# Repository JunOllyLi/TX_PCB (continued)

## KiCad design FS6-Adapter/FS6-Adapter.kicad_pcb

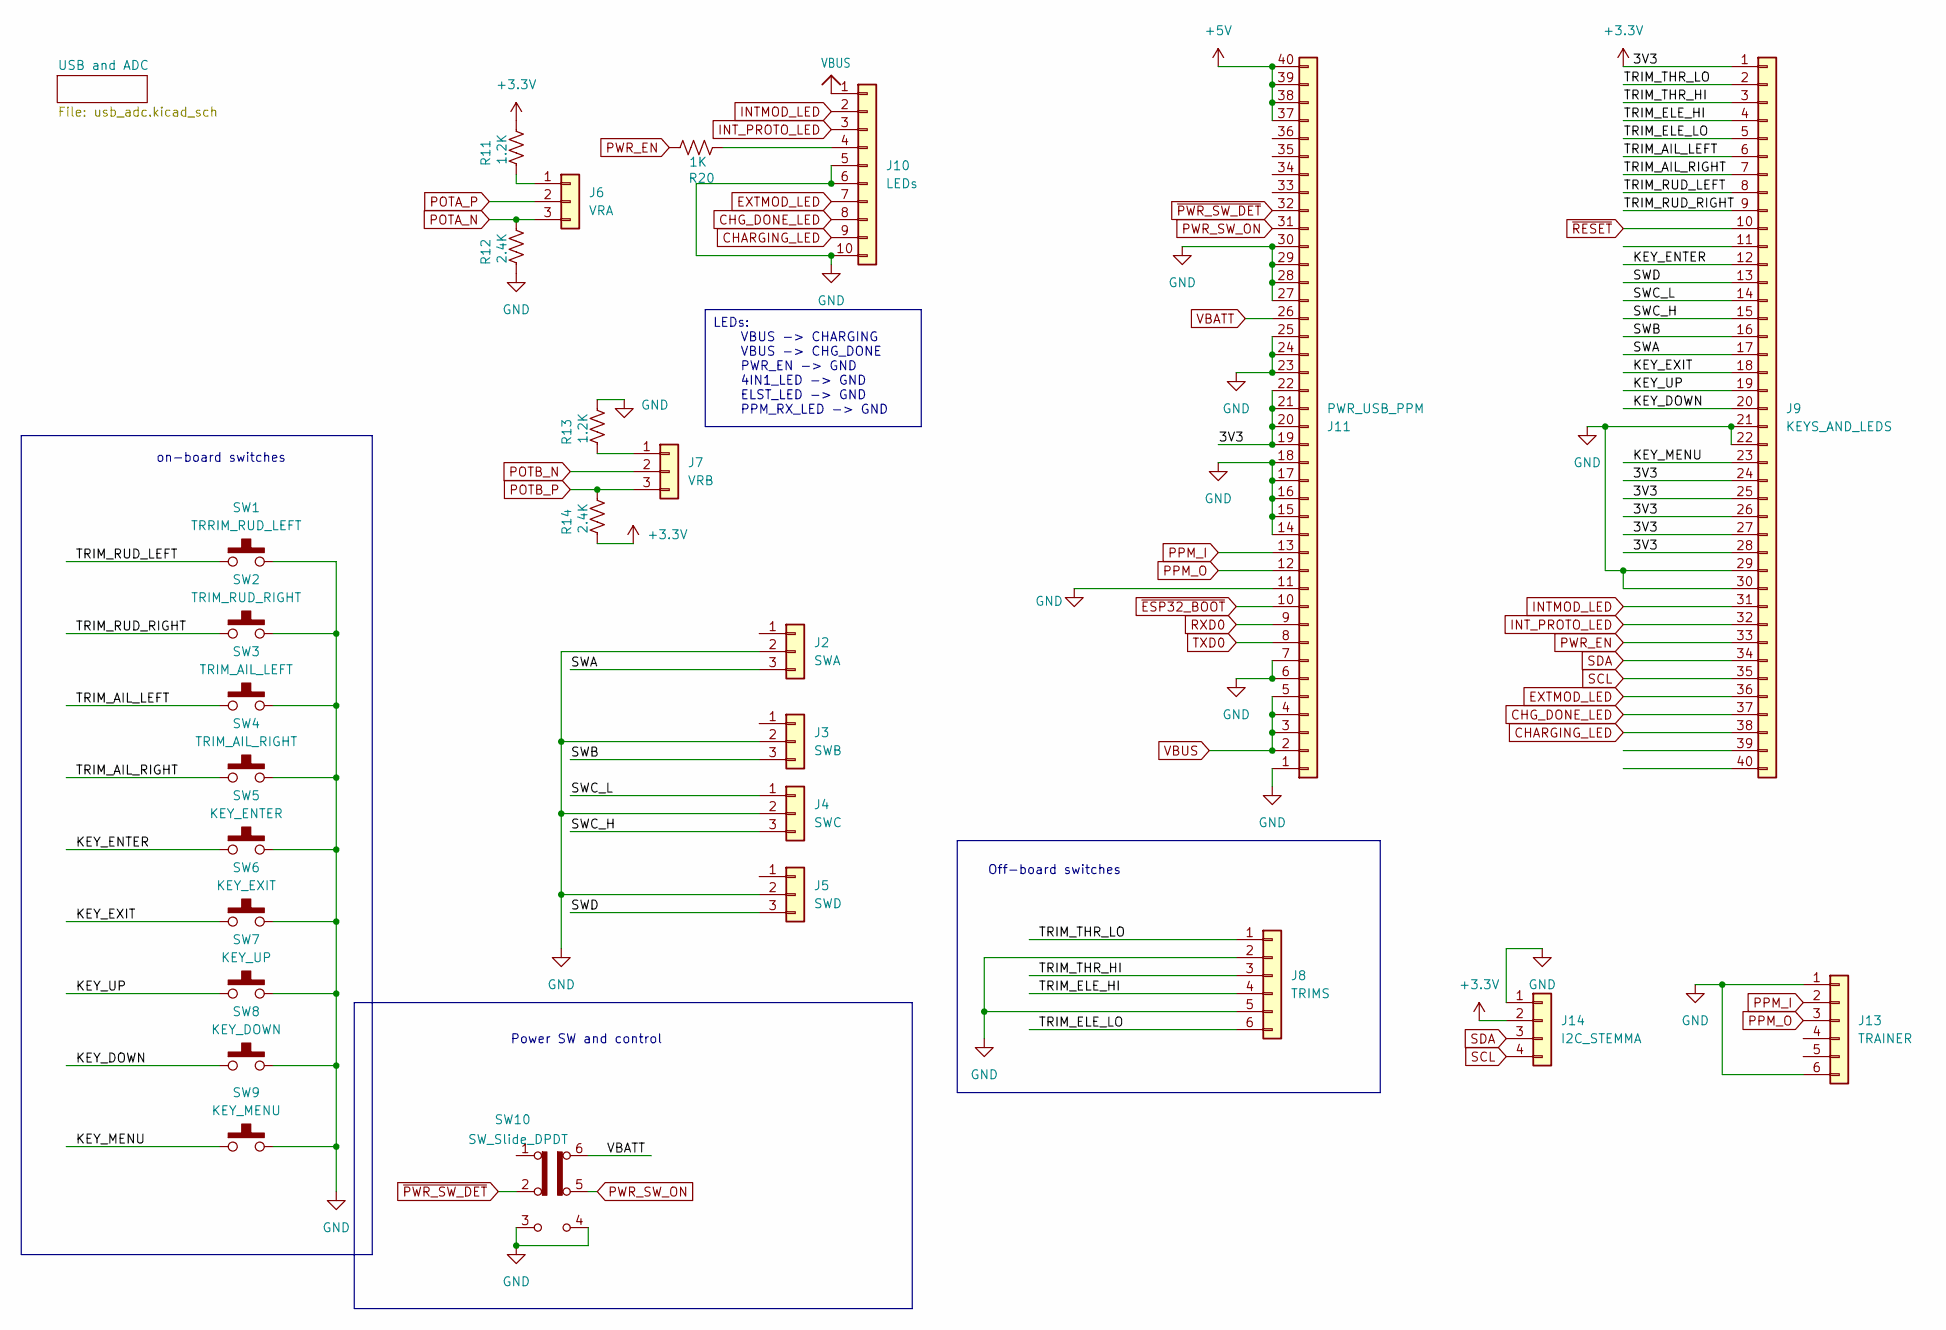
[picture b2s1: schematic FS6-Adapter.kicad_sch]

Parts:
J2: SWA; JST_GH_BM03B-GHS-TBT_1x03-1MP_P1.25mm_Vertical
J3: SWB; JST_GH_BM03B-GHS-TBT_1x03-1MP_P1.25mm_Vertical
J4: SWC; JST_GH_BM03B-GHS-TBT_1x03-1MP_P1.25mm_Vertical
J5: SWD; JST_GH_BM03B-GHS-TBT_1x03-1MP_P1.25mm_Vertical
J6: VRA; JST_GH_BM03B-GHS-TBT_1x03-1MP_P1.25mm_Vertical
J7: VRB; JST_GH_BM03B-GHS-TBT_1x03-1MP_P1.25mm_Vertical
J8: TRIMS; JST_ZH1.50mm_6_PIN_Vertical
J9: KEYS_AND_LEDS; FPC_40PIN_TOP
J10: LEDs; JST_GH_BM10B-GHS-TBT_1x10-1MP_P1.25mm_Vertical
J11: PWR_USB_PPM; FPC_40PIN_TOP
J13: TRAINER; JST_ZH1.50mm_6_PIN_Vertical
J14: I2C_STEMMA; JST_SH_BM04B-SRSS-TB_1x04-1MP_P1.00mm_Vertical
R11, R13: 1.2K; R_0603_1608Metric_Pad0.98x0.95mm_HandSolder
R12, R14: 2.4K; R_0603_1608Metric_Pad0.98x0.95mm_HandSolder
R20: 1K; R_0603_1608Metric_Pad0.98x0.95mm_HandSolder
SW1: TRRIM_RUD_LEFT; SW_6.2mm
SW2: TRIM_RUD_RIGHT; SW_6.2mm
SW3: TRIM_AIL_LEFT; SW_6.2mm
SW4: TRIM_AIL_RIGHT; SW_6.2mm
SW5: KEY_ENTER; SW_6.2mm
SW6: KEY_EXIT; SW_6.2mm
SW7: KEY_UP; SW_6.2mm
SW8: KEY_DOWN; SW_6.2mm
SW9: KEY_MENU; SW_12mm
SW10: SW_Slide_DPDT; SW_SLIDE_DPDT_7mm

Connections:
+3.3V: J9.1, J9.24, J9.25, J9.26, J9.27, J9.28, J11.19, J11.20, J11.21, J11.22, J14.2, R11.2, R14.1; also elsewhere on the board
+5V: J11.37, J11.38, J11.39, J11.40
/KEY_DOWN: J9.20, SW8.1 (A), SW8.2 (B)
/KEY_ENTER: J9.12, SW5.1 (A), SW5.2 (B)
/KEY_EXIT: J9.18, SW6.1 (A), SW6.2 (B)
/KEY_MENU: J9.23, SW9.1 (A), SW9.2 (B)
/KEY_UP: J9.19, SW7.1 (A), SW7.2 (B)
/SWA: J2.3, J9.17
/SWB: J3.3, J9.16
/SWC_H: J4.3, J9.15
/SWC_L: J4.1, J9.14
/SWD: J5.3, J9.13
/TRIM_AIL_LEFT: J9.6, SW3.1 (A), SW3.2 (B)
/TRIM_AIL_RIGHT: J9.7, SW4.1 (A), SW4.2 (B)
/TRIM_ELE_HI: J8.4, J9.4
/TRIM_ELE_LO: J8.6, J9.5
/TRIM_RUD_LEFT: J9.8, SW1.1 (A), SW1.2 (B)
/TRIM_RUD_RIGHT: J9.9, SW2.1 (A), SW2.2 (B)
/TRIM_THR_HI: J8.3, J9.3
/TRIM_THR_LO: J8.1, J9.2
CHARGING_LED: J9.38, J10.9
CHG_DONE_LED: J9.37, J10.8
EXTMOD_LED: J9.36, J10.7
GND: J2.2, J3.2, J4.2, J5.2, J8.2, J8.5, J9.21, J9.22, J9.29, J9.30, J10.5, J10.6, J10.10, J11.1, J11.6, J11.7, J11.11, J11.14, J11.15, J11.16, J11.17, J11.18, J11.23, J11.24, J11.25, J11.27, J11.28, J11.29, J11.30, J13.1, J13.6, J14.1, R12.1, R13.2, SW1.3 (C), SW1.4 (D), SW2.3 (C), SW2.4 (D), SW3.3 (C), SW3.4 (D), SW4.3 (C), SW4.4 (D), SW5.3 (C), SW5.4 (D), SW6.3 (C), SW6.4 (D), SW7.3 (C), SW7.4 (D), SW8.3 (C), SW8.4 (D), SW9.3 (C), SW9.4 (D), SW10.3 (C), SW10.4 (A); also elsewhere on the board
INTMOD_LED: J9.31, J10.2
INT_PROTO_LED: J9.32, J10.3
unnamed: J6.1, R11.1
unnamed: J7.1, R13.1
unnamed: J10.4, R20.1
POTA_N: J6.3, R12.2; also elsewhere on the board
POTA_P: J6.2; also elsewhere on the board
POTB_N: J7.2; also elsewhere on the board
POTB_P: J7.3, R14.2; also elsewhere on the board
PPM_I: J11.13, J13.2
PPM_O: J11.12, J13.3
PWR_EN: J9.33, R20.2
PWR_SW_ON: J11.31, SW10.5 (B)
RXD0: J11.9; also elsewhere on the board
SCL: J9.35, J14.4; also elsewhere on the board
SDA: J9.34, J14.3; also elsewhere on the board
TXD0: J11.8; also elsewhere on the board
VBATT: J11.26, SW10.6 (C); also elsewhere on the board
VBUS: J10.1, J11.2, J11.3, J11.4, J11.5; also elsewhere on the board
~ESP32_BOOT: J11.10; also elsewhere on the board
~PWR_SW_DET: J11.32, SW10.2 (B)
~RESET: J9.10; also elsewhere on the board

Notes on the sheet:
LEDs: VBUS -> CHARGING VBUS -> CHG_DONE PWR_EN -> GND 4IN1_LED -> GND ELST_LED -> GND PPM_RX_LED -> GND
on-board switches
Power SW and control
Off-board switches

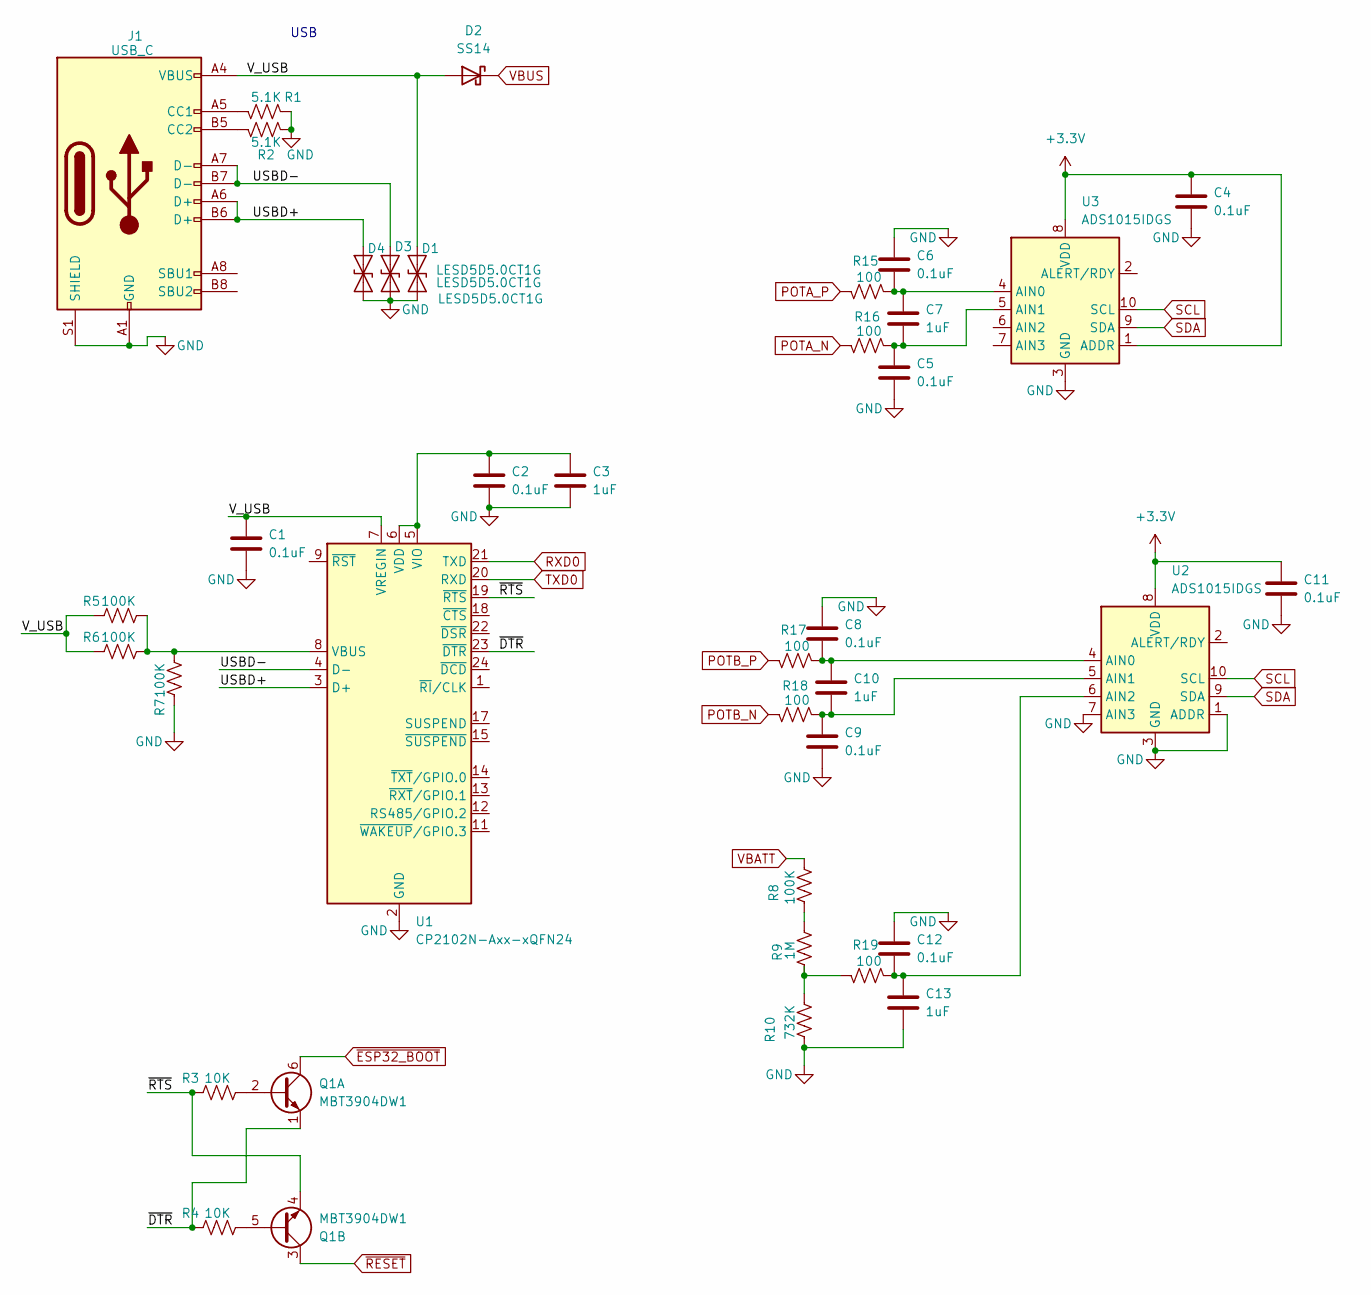
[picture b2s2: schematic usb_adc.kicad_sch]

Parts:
C1, C2, C4, C5, C6, C8, C9, C11, C12: 0.1uF; C_0603_1608Metric_Pad1.08x0.95mm_HandSolder
C3, C7, C10, C13: 1uF; C_0603_1608Metric_Pad1.08x0.95mm_HandSolder
D1, D3, D4: LESD5D5.0CT1G; D_SOD-523
D2: SS14; D_SMA
J1: USB_C; my_USB_C_Receptacle_GCT_USB4105-xx-A_16P_TopMnt_Horizontal
Q1: MBT3904DW1; SOT-363_SC-70-6
R1, R2: 5.1K; R_0603_1608Metric_Pad0.98x0.95mm_HandSolder
R3, R4: 10K; R_0603_1608Metric_Pad0.98x0.95mm_HandSolder
R5, R6, R7, R8: 100K; R_0603_1608Metric_Pad0.98x0.95mm_HandSolder
R9: 1M; R_0603_1608Metric_Pad0.98x0.95mm_HandSolder
R10: 732K; R_0603_1608Metric_Pad0.98x0.95mm_HandSolder
R15, R16, R17, R18, R19: 100; R_0603_1608Metric_Pad0.98x0.95mm_HandSolder
U1: CP2102N-Axx-xQFN24; QFN-24-1EP_4x4mm_P0.5mm_EP2.6x2.6mm
U2, U3: ADS1015IDGS; TSSOP-10_3x3mm_P0.5mm

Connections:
+3.3V: C4.1, C11.1, U2.8 (VDD), U3.1 (ADDR), U3.8 (VDD); also elsewhere on the board
/USB and ADC/USBD+: D4.2 (A2), J1.A6 (D+), J1.B6 (D+), U1.3 (D+)
/USB and ADC/USBD-: D3.2 (A2), J1.A7 (D-), J1.B7 (D-), U1.4 (D-)
/USB and ADC/V_USB: C1.1, D1.2 (A2), D2.2 (A), J1.A4 (VBUS), J1.A9 (VBUS), J1.B4 (VBUS), J1.B9 (VBUS), R5.1, R6.1, U1.7 (VREGIN)
/USB and ADC/~DTR: Q1.1 (E1), R4.1, U1.23 (~DTR)
/USB and ADC/~RTS: Q1.4 (E2), R3.1, U1.19 (~RTS)
GND: C1.2, C2.2, C3.2, C4.2, C5.2, C6.1, C8.1, C9.2, C11.2, C12.1, C13.2, D1.1 (A1), D3.1 (A1), D4.1 (A1), J1.A1 (GND), J1.A12 (GND), J1.B1 (GND), J1.B12 (GND), J1.S1 (SHIELD), R1.1, R2.1, R7.1, R10.1, U1.2 (GND), U1.25 (GND), U2.1 (ADDR), U2.3 (GND), U2.7 (AIN3), U3.3 (GND); also elsewhere on the board
unnamed: J1.A5 (CC1), R1.2
unnamed: J1.B5 (CC2), R2.2
unnamed: Q1.2 (B1), R3.2
unnamed: Q1.5 (B2), R4.2
unnamed: R8.1, R9.2
unnamed: R9.1, R10.2, R19.2
unnamed: R5.2, R6.2, R7.2, U1.8 (VBUS)
unnamed: C2.1, C3.1, U1.5 (VIO), U1.6 (VDD)
unnamed: C8.2, C10.1, R17.1, U2.4 (AIN0)
unnamed: C9.1, C10.2, R18.1, U2.5 (AIN1)
unnamed: C12.2, C13.1, R19.1, U2.6 (AIN2)
unnamed: C6.2, C7.1, R15.1, U3.4 (AIN0)
unnamed: C5.1, C7.2, R16.1, U3.5 (AIN1)
POTA_N: R16.2; also elsewhere on the board
POTA_P: R15.2; also elsewhere on the board
POTB_N: R18.2; also elsewhere on the board
POTB_P: R17.2; also elsewhere on the board
RXD0: U1.21 (TXD); also elsewhere on the board
SCL: U2.10 (SCL), U3.10 (SCL); also elsewhere on the board
SDA: U2.9 (SDA), U3.9 (SDA); also elsewhere on the board
TXD0: U1.20 (RXD); also elsewhere on the board
VBATT: R8.2; also elsewhere on the board
VBUS: D2.1 (K); also elsewhere on the board
~ESP32_BOOT: Q1.6 (C1); also elsewhere on the board
~RESET: Q1.3 (C2); also elsewhere on the board

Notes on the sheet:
USB

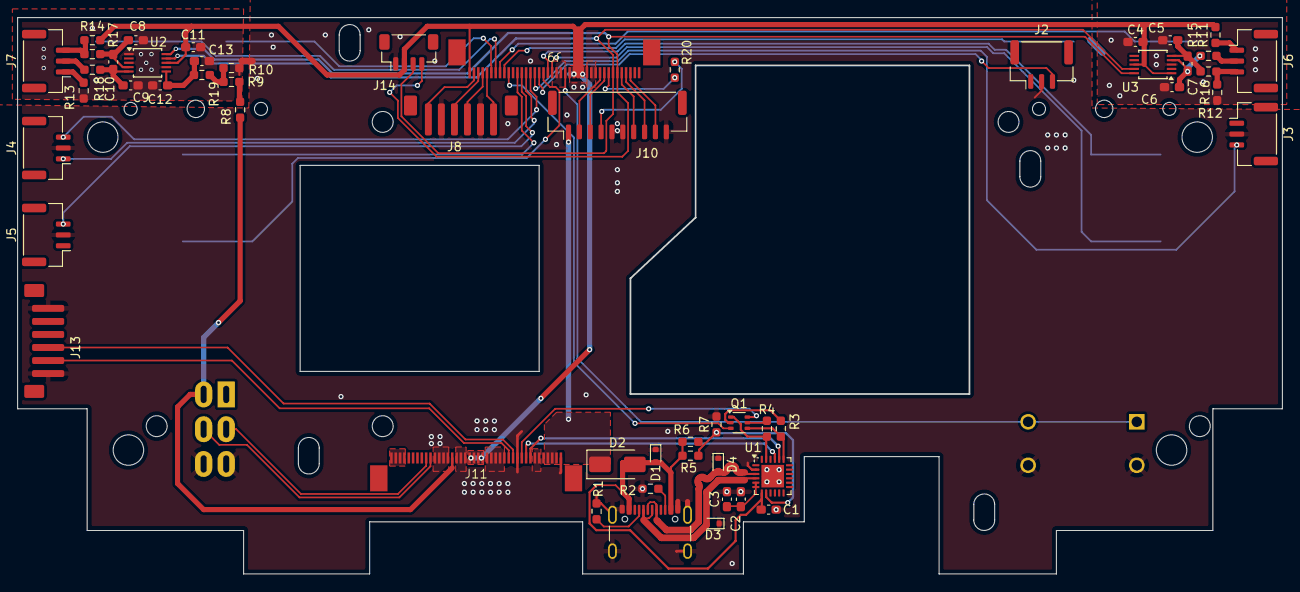
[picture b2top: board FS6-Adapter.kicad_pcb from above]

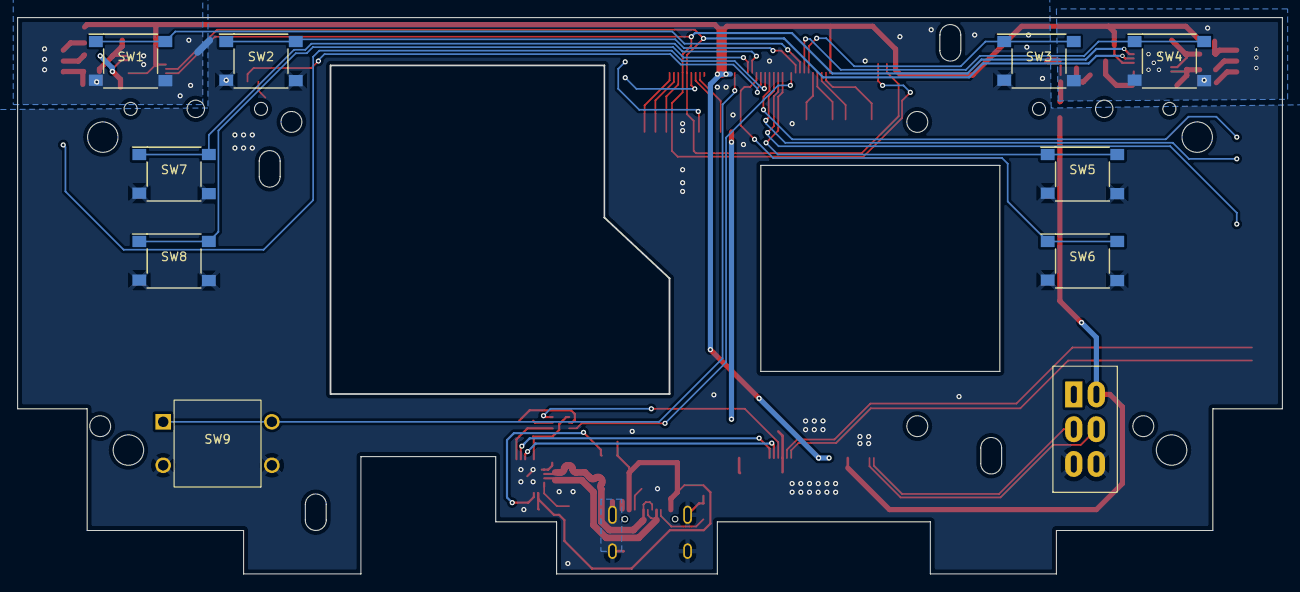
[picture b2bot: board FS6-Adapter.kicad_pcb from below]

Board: 2 copper layers, 145.4 x 63.9 mm, 64 parts (10 on the bottom side), 64 nets.

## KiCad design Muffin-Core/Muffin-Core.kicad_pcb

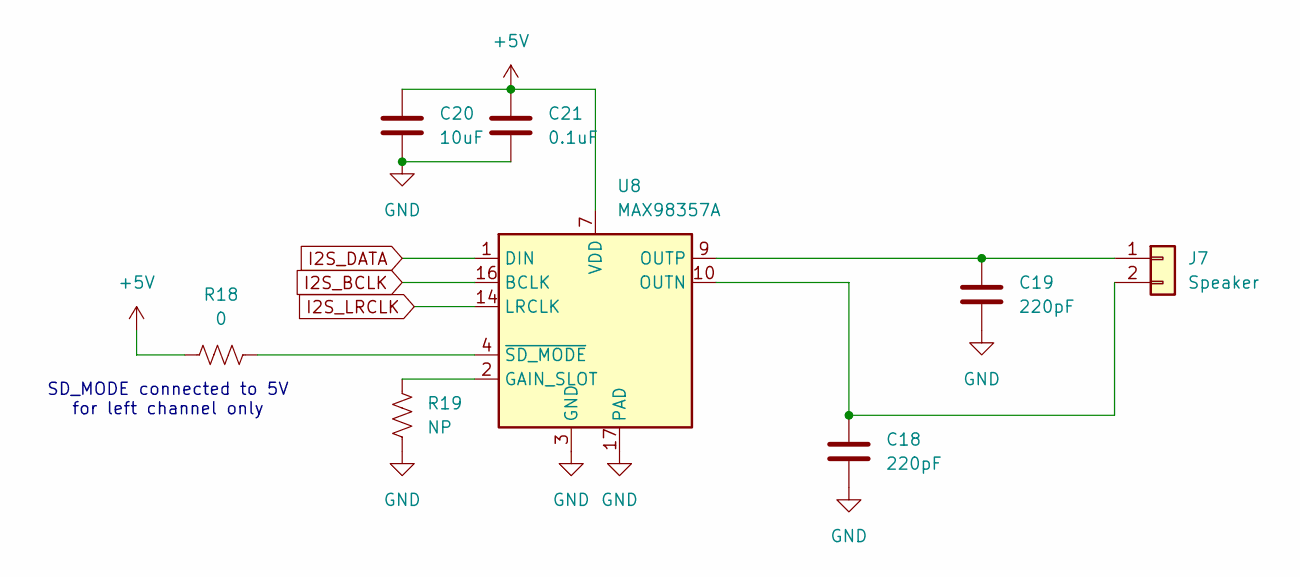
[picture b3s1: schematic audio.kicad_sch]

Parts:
C18, C19: 220pF; C_0603_1608Metric_Pad1.08x0.95mm_HandSolder
C20: 10uF; C_0603_1608Metric_Pad1.08x0.95mm_HandSolder
C21: 0.1uF; C_0603_1608Metric_Pad1.08x0.95mm_HandSolder
J7: Speaker; Molex_PicoBlade_53398-0271_1x02-1MP_P1.25mm_Vertical
R18: 0; R_0603_1608Metric_Pad0.98x0.95mm_HandSolder
R19: NP; R_0603_1608Metric_Pad0.98x0.95mm_HandSolder
U8: MAX98357A; TQFN-16-1EP_3x3mm_P0.5mm_EP1.23x1.23mm

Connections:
+5V: C20.1, C21.1, R18.1, U8.7 (VDD), U8.8 (VDD); also elsewhere on the board
GND: C18.2, C19.2, C20.2, C21.2, R19.1, U8.3 (GND), U8.11 (GND), U8.15 (GND), U8.17 (PAD); also elsewhere on the board
I2S_BCLK: U8.16 (BCLK); also elsewhere on the board
I2S_DATA: U8.1 (DIN); also elsewhere on the board
I2S_LRCLK: U8.14 (LRCLK); also elsewhere on the board
unnamed: C19.1, J7.1, U8.9 (OUTP)
unnamed: C18.1, J7.2, U8.10 (OUTN)
unnamed: R19.2, U8.2 (GAIN_SLOT)
unnamed: R18.2, U8.4 (~SD_MODE)

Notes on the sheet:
SD_MODE connected to 5V for left channel only

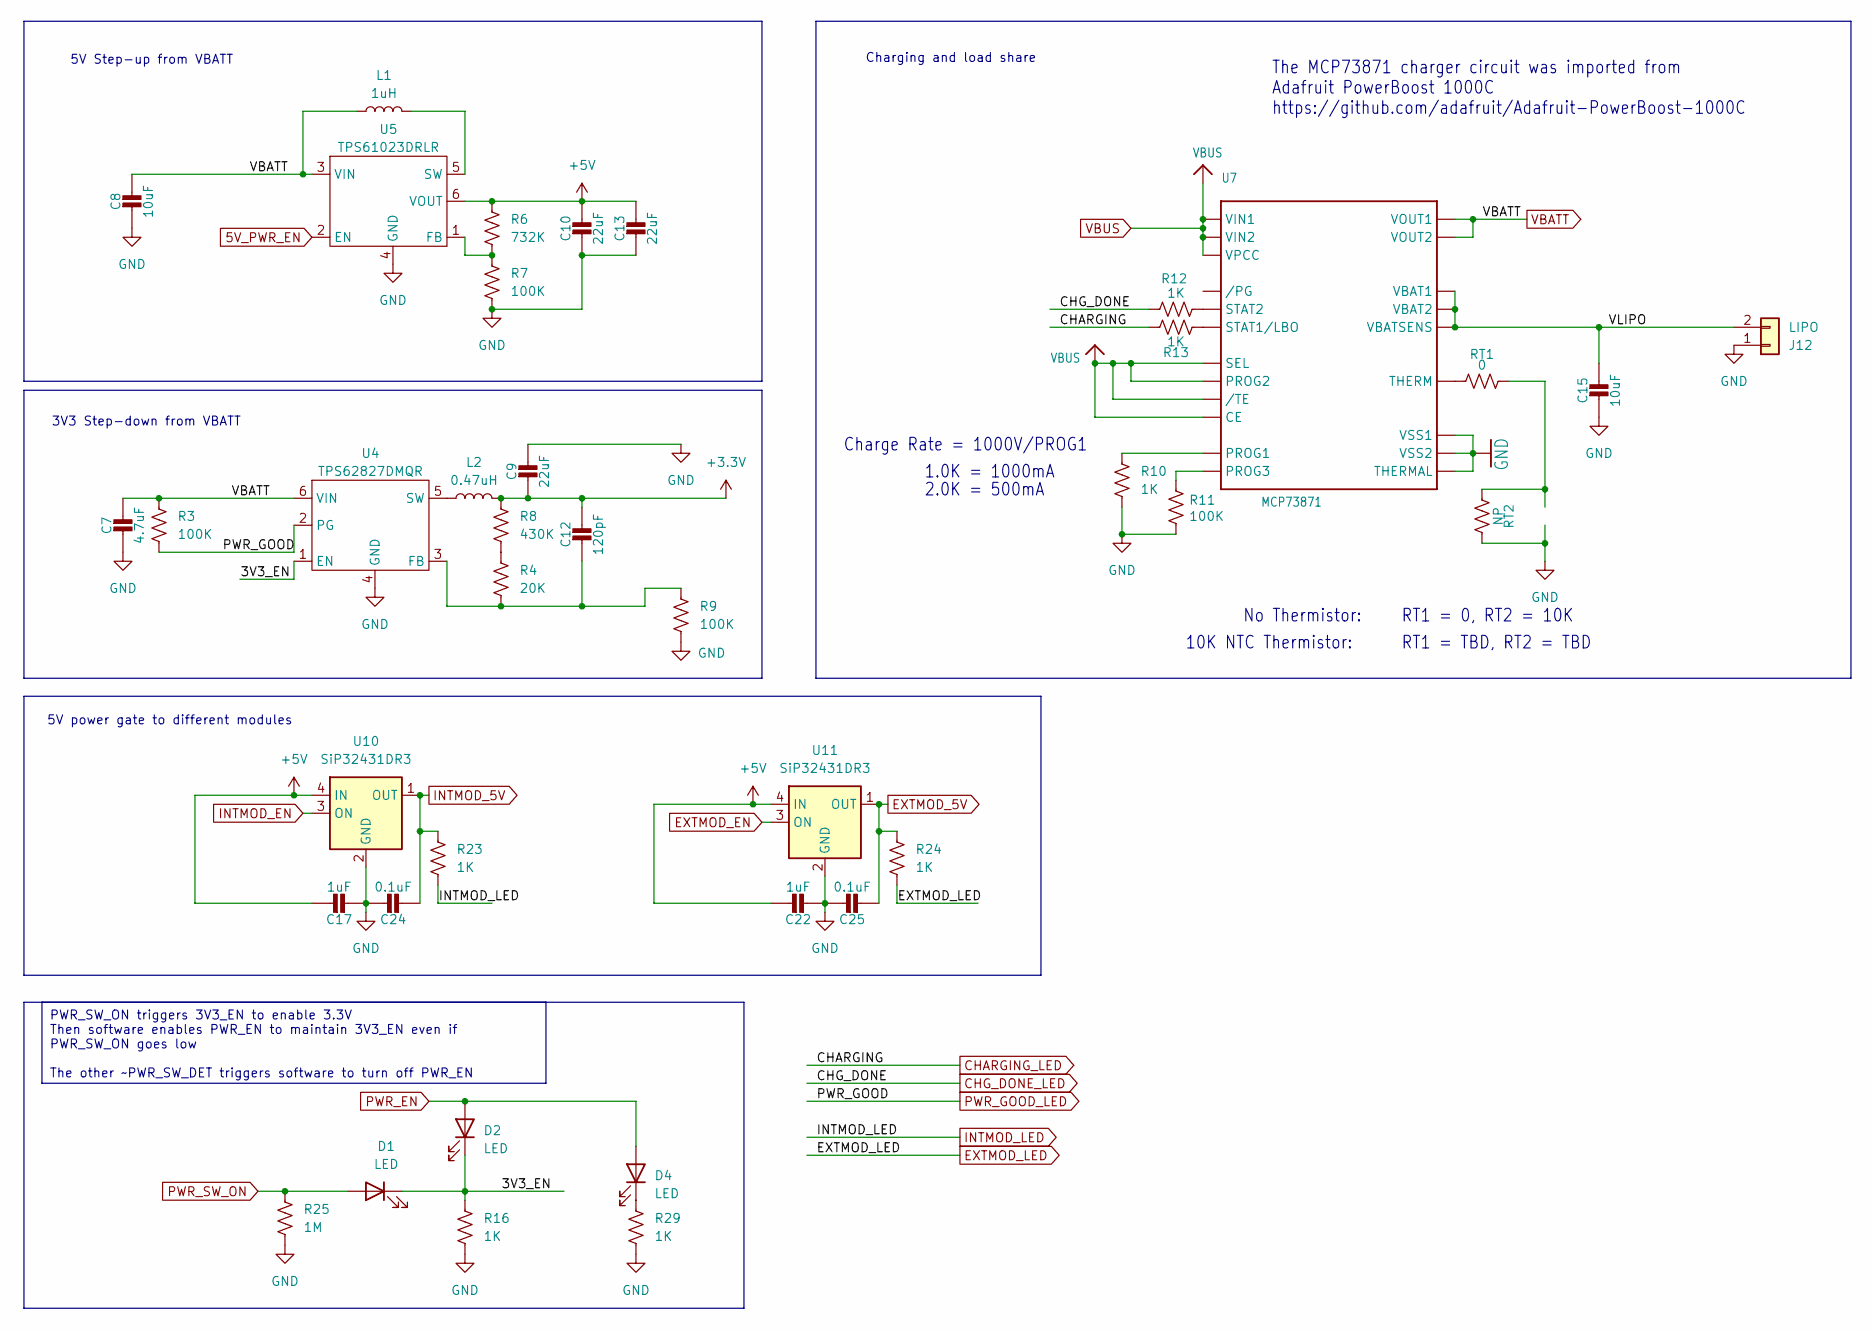
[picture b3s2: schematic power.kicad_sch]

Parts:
C7: 4.7uF; C_0603_1608Metric_Pad1.08x0.95mm_HandSolder
C8, C15: 10uF; C_0603_1608Metric_Pad1.08x0.95mm_HandSolder
C9, C10, C13: 22uF; C_0603_1608Metric_Pad1.08x0.95mm_HandSolder
C12: 120pF; C_0603_1608Metric_Pad1.08x0.95mm_HandSolder
C17, C22: 1uF; C_0603_1608Metric_Pad1.08x0.95mm_HandSolder
C24, C25: 0.1uF; C_0603_1608Metric_Pad1.08x0.95mm_HandSolder
D1, D2, D4: LED; LED_0603_1608Metric_Pad1.05x0.95mm_HandSolder
J12: LIPO; AMASS_XT30UPB-M_1x02_P5.0mm_Vertical
L1: 1uH; L_Cenker_CKCS4020
L2: 0.47uH; L_Cenker_CKCS4020
R3, R7, R9, R11: 100K; R_0603_1608Metric_Pad0.98x0.95mm_HandSolder
R4: 20K; R_0603_1608Metric_Pad0.98x0.95mm_HandSolder
R6: 732K; R_0603_1608Metric_Pad0.98x0.95mm_HandSolder
R8: 430K; R_0603_1608Metric_Pad0.98x0.95mm_HandSolder
R10, R12, R13, R16, R23, R24, R29: 1K; R_0603_1608Metric_Pad0.98x0.95mm_HandSolder
R25: 1M; R_0603_1608Metric_Pad0.98x0.95mm_HandSolder
RT1: 0; R_0603_1608Metric_Pad0.98x0.95mm_HandSolder
RT2: NP; R_0603_1608Metric_Pad0.98x0.95mm_HandSolder
U4: TPS62827DMQR; DMQ_6
U5: TPS61023DRLR; Texas_R-PDSO-N6_DRL-6
U7: MCP73871; QFN-20-1EP_4x4mm_P0.5mm_EP2.5x2.5mm
U10, U11: SiP32431DR3; SOT-363_SC-70-6

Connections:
5V_PWR_EN: U5.2 (EN); also elsewhere on the board
+3.3V: C9.2, C12.1, L2.2, R8.1; also elsewhere on the board
+5V: C10.1, C13.1, C17.1, C22.1, R6.1, U5.6 (VOUT), U10.4 (IN), U11.4 (IN); also elsewhere on the board
/Power/3V3_EN: D1.1 (K), D2.1 (K), R16.1, U4.1 (EN)
/Power/VLIPO: C15.1, J12.2, U7.14 (VBAT1), U7.15 (VBAT2), U7.16 (VBATSENS)
CHARGING_LED: R13.1; also elsewhere on the board
CHG_DONE_LED: R12.1; also elsewhere on the board
EXTMOD_5V: C25.2, R24.1, U11.1 (OUT); also elsewhere on the board
EXTMOD_EN: U11.3 (ON); also elsewhere on the board
EXTMOD_LED: R24.2; also elsewhere on the board
GND: C7.2, C8.2, C9.1, C10.2, C13.2, C15.2, C17.2, C22.2, C24.1, C25.1, J12.1, R7.2, R9.2, R10.2, R11.2, R16.2, R25.2, R29.2, RT2.2, U4.4 (GND), U5.4 (GND), U7.10 (VSS1), U7.11 (VSS2), U7.21 (THERMAL), U10.2 (GND), U10.5 (GND), U11.2 (GND), U11.5 (GND); also elsewhere on the board
INTMOD_5V: C24.2, R23.1, U10.1 (OUT); also elsewhere on the board
INTMOD_EN: U10.3 (ON); also elsewhere on the board
INTMOD_LED: R23.2; also elsewhere on the board
unnamed: D4.1 (K), R29.1
unnamed: R4.1, R8.2
unnamed: RT1.2, RT2.1
unnamed: C12.2, R4.2, R9.1, U4.3 (FB)
unnamed: L2.1, U4.5 (SW)
unnamed: R6.2, R7.1, U5.1 (FB)
unnamed: L1.2, U5.5 (SW)
unnamed: R10.1, U7.13 (PROG1)
unnamed: R11.1, U7.12 (PROG3)
unnamed: R13.2, U7.8 (STAT1/LBO)
unnamed: R12.2, U7.7 (STAT2)
unnamed: RT1.1, U7.5 (THERM)
PWR_EN: D2.2 (A), D4.2 (A); also elsewhere on the board
PWR_GOOD_LED: R3.2, U4.2 (PG)
PWR_SW_ON: D1.2 (A), R25.1; also elsewhere on the board
VBATT: C7.1, C8.1, L1.1, R3.1, U4.6 (VIN), U5.3 (VIN), U7.1 (VOUT1), U7.20 (VOUT2); also elsewhere on the board
VBUS: U7.2 (VPCC), U7.3 (SEL), U7.4 (PROG2), U7.9 (/TE), U7.17 (CE), U7.18 (VIN1), U7.19 (VIN2); also elsewhere on the board

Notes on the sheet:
PWR_SW_ON triggers 3V3_EN to enable 3.3V Then software enables PWR_EN to maintain 3V3_EN even if PWR_SW_ON goes low The other ~PWR_SW_DET triggers software to turn off PWR_EN
The MCP73871 charger circuit was imported from Adafruit PowerBoost 1000C https://github.com/adafruit/Adafruit-PowerBoost-1000C
5V power gate to different modules
3V3 Step-down from VBATT
Charge Rate = 1000V/PROG1
RT1 = 0, RT2 = 10K
10K NTC Thermistor:
RT1 = TBD, RT2 = TBD
5V Step-up from VBATT
1.0K = 1000mA
Charging and load share
2.0K = 500mA
No Thermistor:

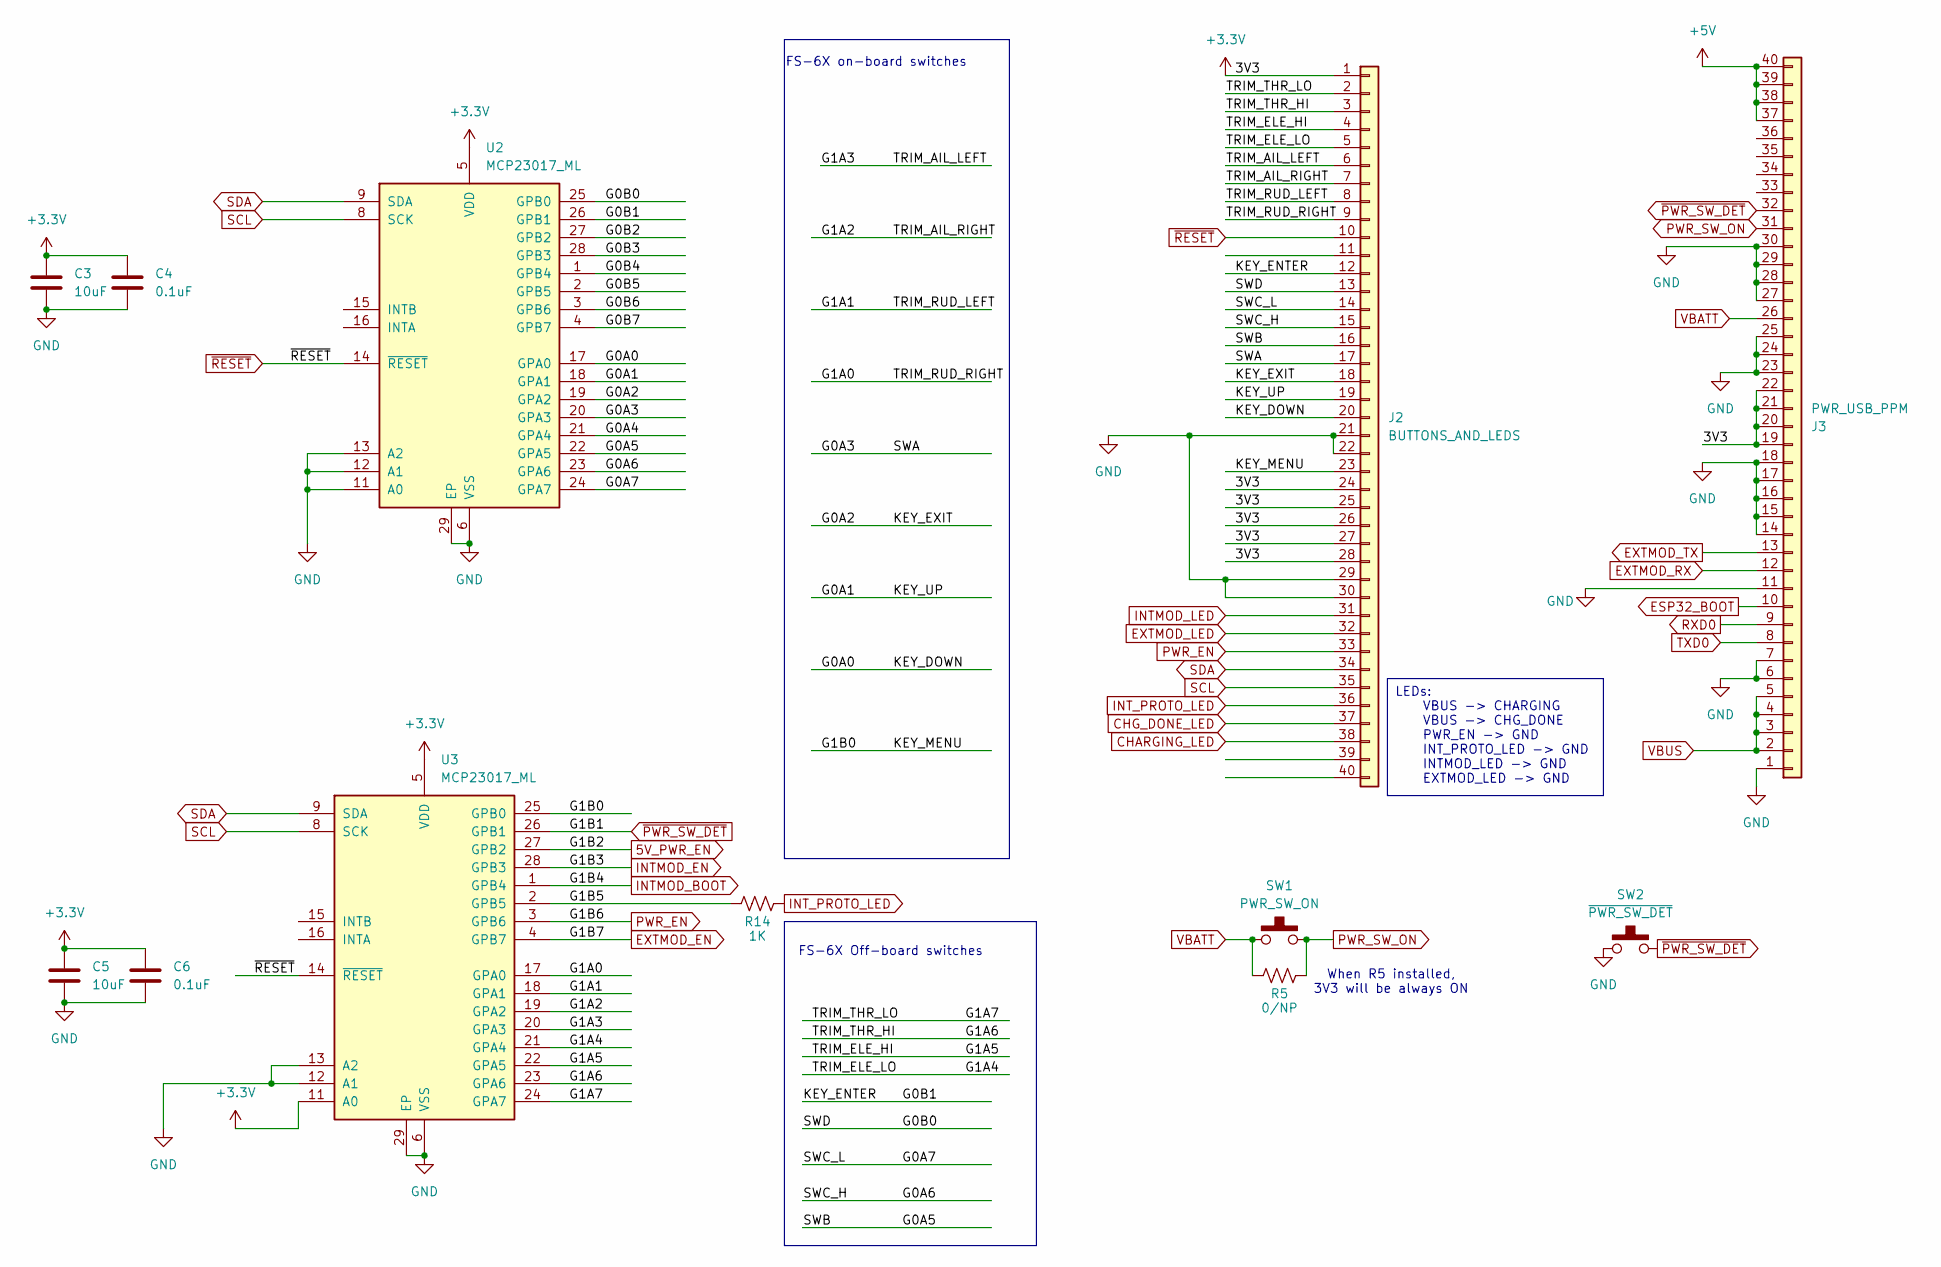
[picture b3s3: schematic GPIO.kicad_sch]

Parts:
C3, C5: 10uF; C_0603_1608Metric_Pad1.08x0.95mm_HandSolder
C4, C6: 0.1uF; C_0603_1608Metric_Pad1.08x0.95mm_HandSolder
J2: BUTTONS_AND_LEDS; FPC_40PIN_TOP
J3: PWR_USB_PPM; FPC_40PIN_TOP
R5: 0/NP; R_0603_1608Metric_Pad0.98x0.95mm_HandSolder
R14: 1K; R_0603_1608Metric_Pad0.98x0.95mm_HandSolder
SW1: PWR_SW_ON; SW_3x4mm_2pin
SW2: ~{PWR_SW_DET}; SW_3x4mm_2pin
U2, U3: MCP23017_ML; QFN-28-1EP_6x6mm_P0.65mm_EP4.25x4.25mm

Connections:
5V_PWR_EN: U3.27 (GPB2); also elsewhere on the board
+3.3V: C3.1, C4.1, C5.1, C6.1, J2.1, J2.24, J2.25, J2.26, J2.27, J2.28, J3.19, J3.20, J3.21, J3.22, U2.5 (VDD), U3.5 (VDD), U3.11 (A0); also elsewhere on the board
+5V: J3.37, J3.38, J3.39, J3.40; also elsewhere on the board
/GPIO_ext/G0A0: J2.20, U2.17 (GPA0)
/GPIO_ext/G0A1: J2.19, U2.18 (GPA1)
/GPIO_ext/G0A2: J2.18, U2.19 (GPA2)
/GPIO_ext/G0A3: J2.17, U2.20 (GPA3)
/GPIO_ext/G0A4: U2.21 (GPA4)
/GPIO_ext/G0A5: J2.16, U2.22 (GPA5)
/GPIO_ext/G0A6: J2.15, U2.23 (GPA6)
/GPIO_ext/G0A7: J2.14, U2.24 (GPA7)
/GPIO_ext/G0B0: J2.13, U2.25 (GPB0)
/GPIO_ext/G0B1: J2.12, U2.26 (GPB1)
/GPIO_ext/G0B2: U2.27 (GPB2)
/GPIO_ext/G0B3: U2.28 (GPB3)
/GPIO_ext/G0B4: U2.1 (GPB4)
/GPIO_ext/G0B5: U2.2 (GPB5)
/GPIO_ext/G0B6: U2.3 (GPB6)
/GPIO_ext/G0B7: U2.4 (GPB7)
/GPIO_ext/G1A0: J2.9, U3.17 (GPA0)
/GPIO_ext/G1A1: J2.8, U3.18 (GPA1)
/GPIO_ext/G1A2: J2.7, U3.19 (GPA2)
/GPIO_ext/G1A3: J2.6, U3.20 (GPA3)
/GPIO_ext/G1A4: J2.5, U3.21 (GPA4)
/GPIO_ext/G1A5: J2.4, U3.22 (GPA5)
/GPIO_ext/G1A6: J2.3, U3.23 (GPA6)
/GPIO_ext/G1A7: J2.2, U3.24 (GPA7)
/GPIO_ext/G1B0: J2.23, U3.25 (GPB0)
/GPIO_ext/G1B5: R14.1, U3.2 (GPB5)
CHARGING_LED: J2.38; also elsewhere on the board
CHG_DONE_LED: J2.37; also elsewhere on the board
ESP32_BOOT: J3.10; also elsewhere on the board
EXTMOD_EN: U3.4 (GPB7); also elsewhere on the board
EXTMOD_LED: J2.32; also elsewhere on the board
EXTMOD_RX: J3.12; also elsewhere on the board
EXTMOD_TX: J3.13; also elsewhere on the board
GND: C3.2, C4.2, C5.2, C6.2, J2.21, J2.22, J2.29, J2.30, J3.1, J3.6, J3.7, J3.11, J3.14, J3.15, J3.16, J3.17, J3.18, J3.23, J3.24, J3.25, J3.27, J3.28, J3.29, J3.30, SW2.1 (2), U2.6 (VSS), U2.11 (A0), U2.12 (A1), U2.13 (A2), U2.29 (EP), U3.6 (VSS), U3.12 (A1), U3.13 (A2), U3.29 (EP); also elsewhere on the board
INTMOD_BOOT: U3.1 (GPB4); also elsewhere on the board
INTMOD_EN: U3.28 (GPB3); also elsewhere on the board
INTMOD_LED: J2.31; also elsewhere on the board
INT_PROTO_LED: J2.36, R14.2
PWR_EN: J2.33, U3.3 (GPB6); also elsewhere on the board
PWR_SW_ON: J3.31, R5.2, SW1.2; also elsewhere on the board
RXD0: J3.9; also elsewhere on the board
SCL: J2.35, U2.8 (SCK), U3.8 (SCK); also elsewhere on the board
SDA: J2.34, U2.9 (SDA), U3.9 (SDA); also elsewhere on the board
TXD0: J3.8; also elsewhere on the board
VBATT: J3.26, R5.1, SW1.1 (2); also elsewhere on the board
VBUS: J3.2, J3.3, J3.4, J3.5; also elsewhere on the board
~PWR_SW_DET: J3.32, SW2.2, U3.26 (GPB1)
~RESET: J2.10, U2.14 (~RESET), U3.14 (~RESET); also elsewhere on the board

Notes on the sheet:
LEDs: VBUS -> CHARGING VBUS -> CHG_DONE PWR_EN -> GND INT_PROTO_LED -> GND INTMOD_LED -> GND EXTMOD_LED -> GND
FS-6X on-board switches
FS-6X Off-board switches
When R5 installed, 3V3 will be always ON
